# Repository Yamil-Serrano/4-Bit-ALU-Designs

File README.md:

# 4-Bit ALU Designs

A collection of 4-bit ALU implementations built entirely from discrete 74HC-series logic ICs. The project begins with a minimal ripple-carry architecture assembled on breadboard, then evolves into an expanded design featuring a 3-bit operation code and a dedicated PCB layout demonstrating how arithmetic and logic operations can be derived from fundamental gate-level building blocks.

# Hardware-Minimalist 4-bit ALU
This ALU represents the most fundamental version of the project: a design built entirely from discrete logic ICs, assembled by hand using breadboards, wiring, and basic digital components. The core idea is to show how a complete arithmetic and logic system can emerge from a minimal set of building blocks, following the principles of NAND universality and simple ripple-carry computation.

At its heart, this design implements a 4-bit ripple-carry adder, where each bit calculates its sum and pass its carry to the next stage. While not the fastest architecture, its transparency makes it highly educational: every step of the computation from XOR-based addition to AND-driven carry generation is physically observable in the circuit.

Beyond addition and subtraction, the ALU includes a NAND-based logic path to highlight how a single universal gate can serve as the foundation for more complex operations. The result is a compact but fully functional ALU that exemplifies hardware minimalism, discrete logic design, and hands-on digital engineering.

## Technical Specifications

### Core Features
- **Data Width**: 4-bit parallel processing
- **Operations**: 
  - `00` - Bitwise NAND (A NAND B)
  - `01` - Arithmetic addition (A + B)
  - `11` - Arithmetic subtraction (A - B) using two's complement
- **Control Input**: 2-bit operation code
- **Output Flags**: 
  - **Carry Out** - For arithmetic overflow detection
  - **Zero Flag** - Indicates when result equals 0000
- **Design Philosophy**: Hardware minimalism via NAND universality

## Integrated Circuits Used
| IC          | Function        | Quantity | Purpose                                        |
| ----------- | --------------- | -------- | ---------------------------------------------- |
| **74HC86**  | Quad XOR Gate   | 4        | Full adder implementation and two's complement |
| **74HC08**  | Quad AND Gate   | 2        | Carry generation for arithmetic operations     |
| **74HC00**  | Quad NAND Gate  | 1        | NAND operation and control logic               |
| **74HC157** | 2:1 Multiplexer | 1        | Operation selection and output routing         |
| **74HC4002**| Dual 4-Input NOR Gate | 1        | Zero detection             |

**Total Components:** 9 ICs implementing a complete 4-bit ALU

## Hardware Implementation

### Circuit Design

## Operation Details

#### 1. **Addition (01)**
- Implements 4-bit ripple-carry adder
- Uses XOR gates for sum, AND gates for carry
- Direct A + B computation

#### 2. **Subtraction (11)**
- Utilizes two's complement method
- Inverts B using XOR gates (B ⊕ 1)
- Adds 1 via carry-in for proper complement
- Result: A + (~B + 1) = A - B

#### 3. **NAND Operation (00)**
- Direct NAND gate implementation
- Demonstrates NAND universality principle
- Basis for emulating all other logic operations

### Flag Generation

#### **Zero Flag**
- Implemented using **74HC4002 Zero Detection Unit**
- Output: HIGH when result = 0000

#### **Carry Flag**
- Generated from the 4th full adder's carry-out
- Indicates arithmetic overflow in addition/subtraction

## Truth Table Examples

| A (bin) | B (bin) | Op | Result | Carry | Zero |
|---------|---------|----|--------|-------|------|
| 0101    | 0011    | 01 (Add) | 1000 | 0 | 0 |
| 0111    | 0010    | 11 (Sub) | 0101 | 1 | 0 |
| 1111    | 1111    | 00 (NAND) | 0000 | X | 1 |
| 0000    | 0000    | 01 (Add) | 0000 | 0 | 1 |

## Educational Value

This project demonstrates fundamental computer architecture concepts:

1. **NAND Universality**: All digital logic can be constructed from NAND gates
2. **Two's Complement Arithmetic**: How computers perform subtraction
3. **Hardware/Software Trade-off**: Why some operations are emulated in software
4. **Flag-Based Computing**: Essential for conditional operations in CPUs
5. **Ripple-Carry Design**: Basic but functional adder architecture

## ⚠️ Known Limitations

1. **Propagation Delay**: Ripple-carry design limits maximum speed
2. **Limited Operations**: Only 3 hardware operations
3. **No Overflow Flag**: Signed overflow detection not implemented

# Hardware-Minimalist 4-bit ALU (Modified 3-bit OP Code)

This updated version of the 4-bit minimalistic ALU introduces expanded operation selection while maintaining a fully discrete IC implementation. By replacing the 74HC157 with two 74HC153 multiplexers, the ALU can now handle five distinct operations controlled by a 3-bit operation code.

### Core Features

* **Data Width**: 4-bit parallel processing
* **Operations**:

  * `000` - Arithmetic Addition (A + B)
  * `100` - Arithmetic Subtraction (A - B) using two's complement
  * `X01` - Bitwise NAND (A NAND B)
  * `X10` - Bitwise XOR (A XOR B)
  * `X11` - Bitwise NOR (A NOR B)
* **Control Input**: 3-bit operation code
* **Output Flags**:

  * **Equal Flag** - Indicates when A equals B
  * **Zero Flag** - Indicates when ALU result equals 0000

### Integrated Circuits Used

| IC          | Function                   | Quantity | Purpose                                        |
| ----------- | -------------------------- | -------- | ---------------------------------------------- |
| **74HC86**  | Quad XOR Gate              | 5        | Full adder, two's complement, XOR operation    |
| **74HC08**  | Quad AND Gate              | 2        | Carry generation for arithmetic operations     |
| **74HC00**  | Quad NAND Gate             | 1        | NAND operation                                 |
| **74HC153** | Dual 4-input Multiplexer   | 2        | Selection between arithmetic and logic outputs |
| **74HC02**  | Quad NOR Gate              | 1        | NOR operation                                  |
| **74HC4002**| Dual 4-Input NOR Gate      | 1        | Zero and Equality detection                    |

**Total Components**: 12 ICs, implementing a complete 4-bit ALU with expanded functionality

## Hardware Implementation

### Circuit Design

### PCB Design in Kicad

After validating the architecture in simulation, the design was 
migrated from breadboard to a custom PCB manufactured via JLCPCB. 
Each IC is paired with a dedicated 100nF ceramic bypass capacitor
placed directly at the power pins to suppress switching noise. 
A 100µF bulk electrolytic capacitor stabilizes the 5V supply rail.

### Physical Build

## Verification & Test Bench

To validate correct operation across all input combinations, a dedicated test bench was developed using an ESP32 microcontroller. The [`firmware`](./src/tester/src) exhaustively tests all 256 input combinations (A × B, 0–15) for each of the 8 opcode states, and verifies both output flags across all cases totaling 2,048 flag assertions for the Zero flag alone.
All five operations passed with 100% accuracy across every input combination. Both the Equal flag and Zero flag returned correct results in every tested case. Results are reported over Serial with ANSI color coding, distinguishing passing opcodes in green from partial matches in yellow. A 20×4 LCD display connected via I2C provides a real-time progress bar during testing and a summary screen upon completion.

### Operation Details

#### 1. **Arithmetic Addition (000)**

* Implements 4-bit ripple-carry adder
* Uses XOR gates for sum, AND gates for carry
* Direct A + B computation

#### 2. **Arithmetic Subtraction (100)**

* Utilizes two's complement method
* Inverts B using XOR gates and adds 1 via carry-in
* Result: A + (~B + 1) = A - B

#### 3. **Bitwise NAND (X01)**

* Uses 74HC00 to implement NAND logic

#### 4. **Bitwise XOR (X10)**

* Uses additional 74HC86 to implement XOR logic

#### 5. **Bitwise NOR (X11)**

* Uses 74HC02 to implement NOR logic

### Flag Generation (Implemented using **74HC4002**)

* **Zero Flag**: HIGH when ALU output is 0000
* **Equal Flag**: HIGH when A is equal to B

### Truth Table Examples

| A (bin) | B (bin) | Op         | Result | Zero | Equal |
| ------- | ------- | ---------- | ------ | ---- | ----- |
| 0101    | 0011    | 000 (Add)  | 1000   | 0    | 0     |
| 0111    | 0010    | 100 (Sub)  | 0101   | 0    | 0     |
| 1111    | 1111    | X01 (NAND) | 0000   | 1    | 1     |
| 1010    | 0101    | X10 (XOR)  | 1111   | 0    | 0     |
| 1100    | 1010    | X11 (NOR)  | 0001   | 0    | 0     |

# FPGA Implementation: Tang Nano 9K
This module ports the 4-bit ALU logic from discrete integrated circuits to a programmable Gowin GW1NR-LV9 FPGA on the Sipeed Tang Nano 9K board. This transformation demonstrates a key modern digital design workflow: translating a proven hardware concept into a compact, single-chip solution using Hardware Description Language (HDL). The implementation faithfully replicates the behavior of the original breadboard circuit, providing a direct comparison between discrete and programmable logic.

## Physical Prototype & Interfacing
The FPGA interacts with the physical world through a simple, hands-on interface built on a breadboard. This setup mirrors the experience of the discrete version while showcasing the FPGA's role as a universal logic device.

## Design Philosophy & Notes
- **Architectural Fidelity**: The HDL description was structured to mirror the original ripple-carry data path, providing a clear one-to-one conceptual mapping between the discrete gate-level design and its HDL counterpart.
- **Resource Efficiency**: The entire system utilizes a very small fraction of the FPGA's available logic cells, demonstrating how a functional digital system can be miniaturized onto modern programmable logic.
- **Practical Focus**: The primary goal was a correct and understandable translation to HDL rather than performance optimization, maintaining the project's core educational value.

## Comparative Summary: Discrete vs. FPGA
This implementation highlights the practical differences between two hardware paradigms.

| Aspect | Discrete IC Implementation | FPGA Implementation |
| :--- | :--- | :--- |
| **Component Count** | 9 to 12 ICs, extensive wiring. | **1** primary chip. |
| **Design Method** | Wiring logic gates on a breadboard. | Writing and synthesizing HDL code. |
| **Flexibility** | Fixed; changes require physical rewiring. | **Reconfigurable** via code upload. |
| **Debugging** | Direct probing of every net with a multimeter. | Indirect, relying on synthesis reports and output observation. |
| **Core Experience** | Understanding gate-level data flow and propagation delay. | Learning the FPGA toolchain and HDL design patterns. |

## License
Licensed under the **Solderpad Hardware License v2.1**.  
See the [LICENSE](LICENSE-HARDWARE) file for full terms.

## Contact
If you have any questions or suggestions, feel free to reach out:
- **GitHub:** [Neowizen](https://github.com/Yamil-Serrano)

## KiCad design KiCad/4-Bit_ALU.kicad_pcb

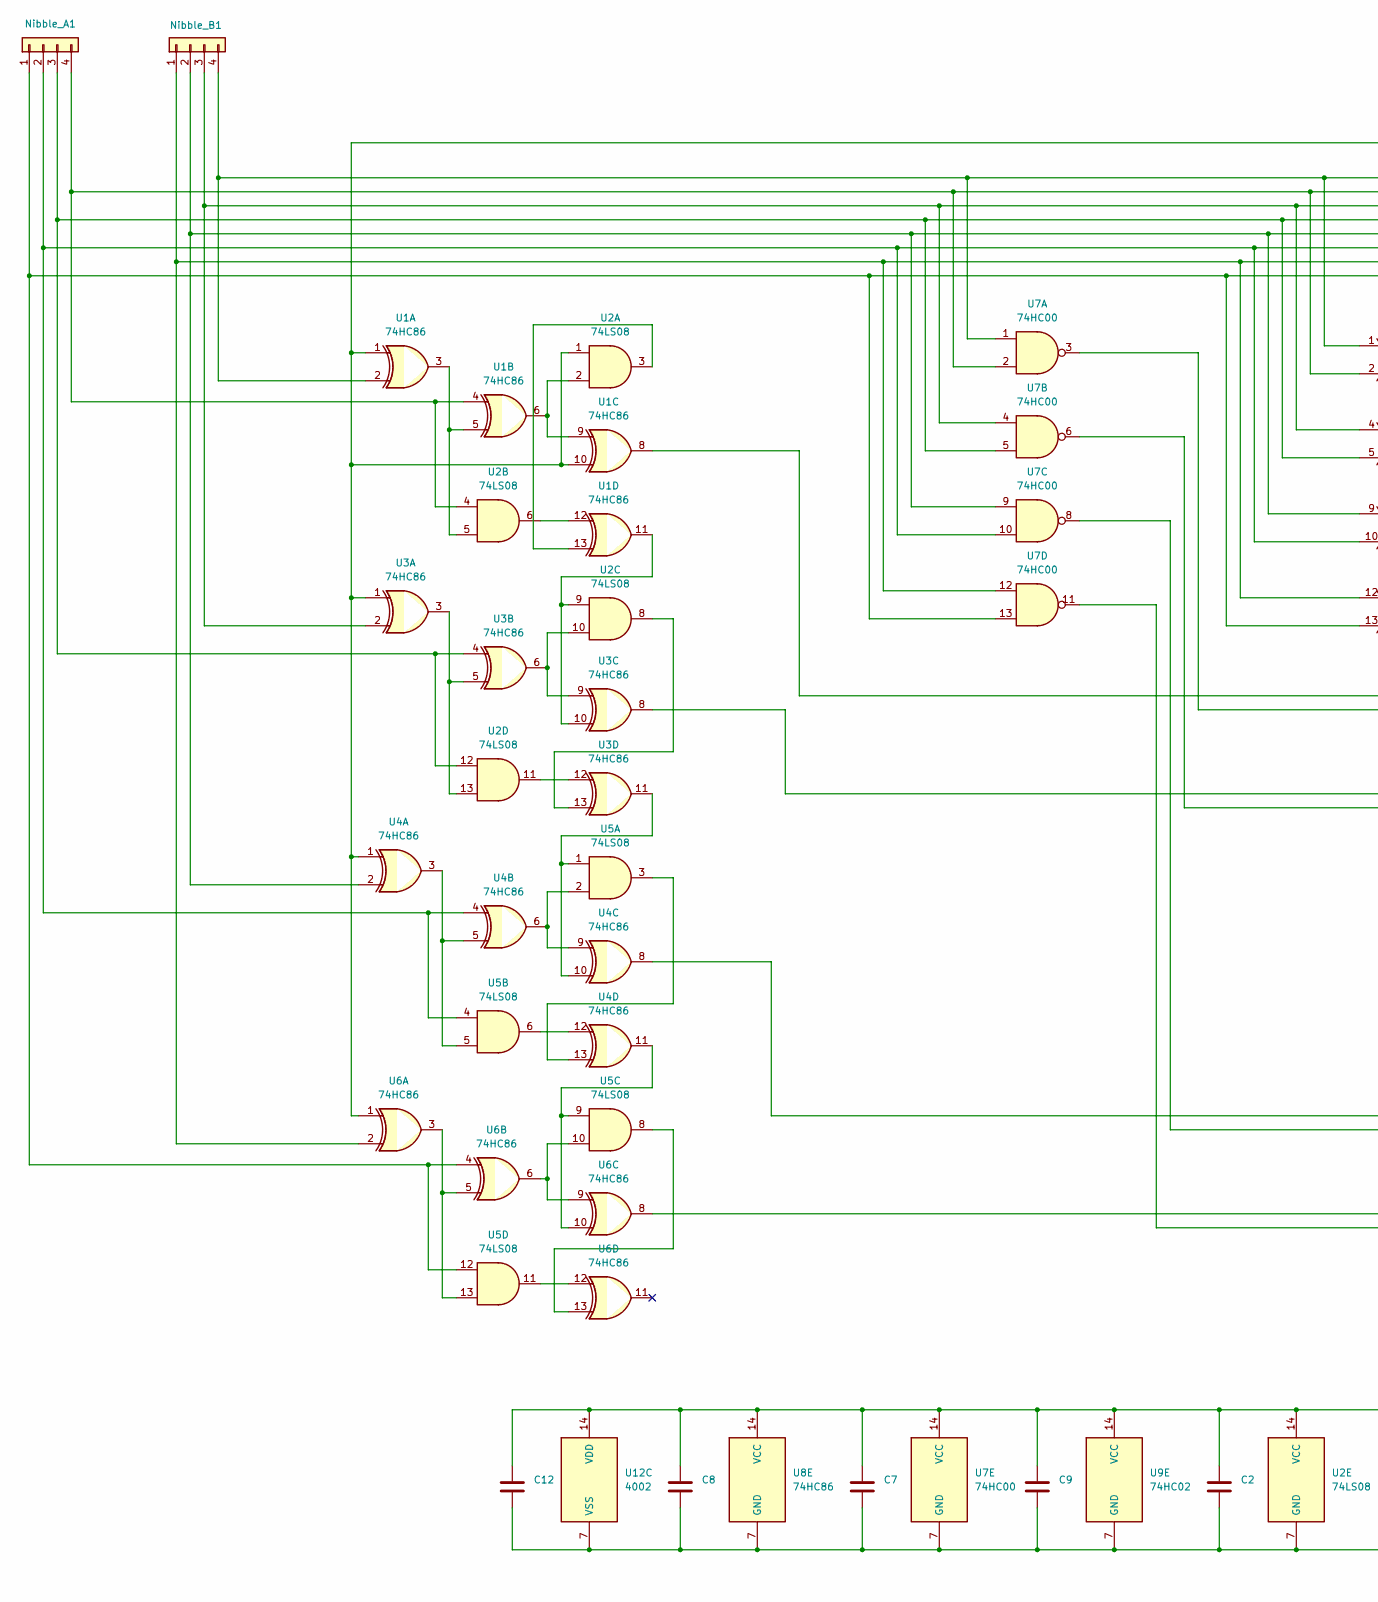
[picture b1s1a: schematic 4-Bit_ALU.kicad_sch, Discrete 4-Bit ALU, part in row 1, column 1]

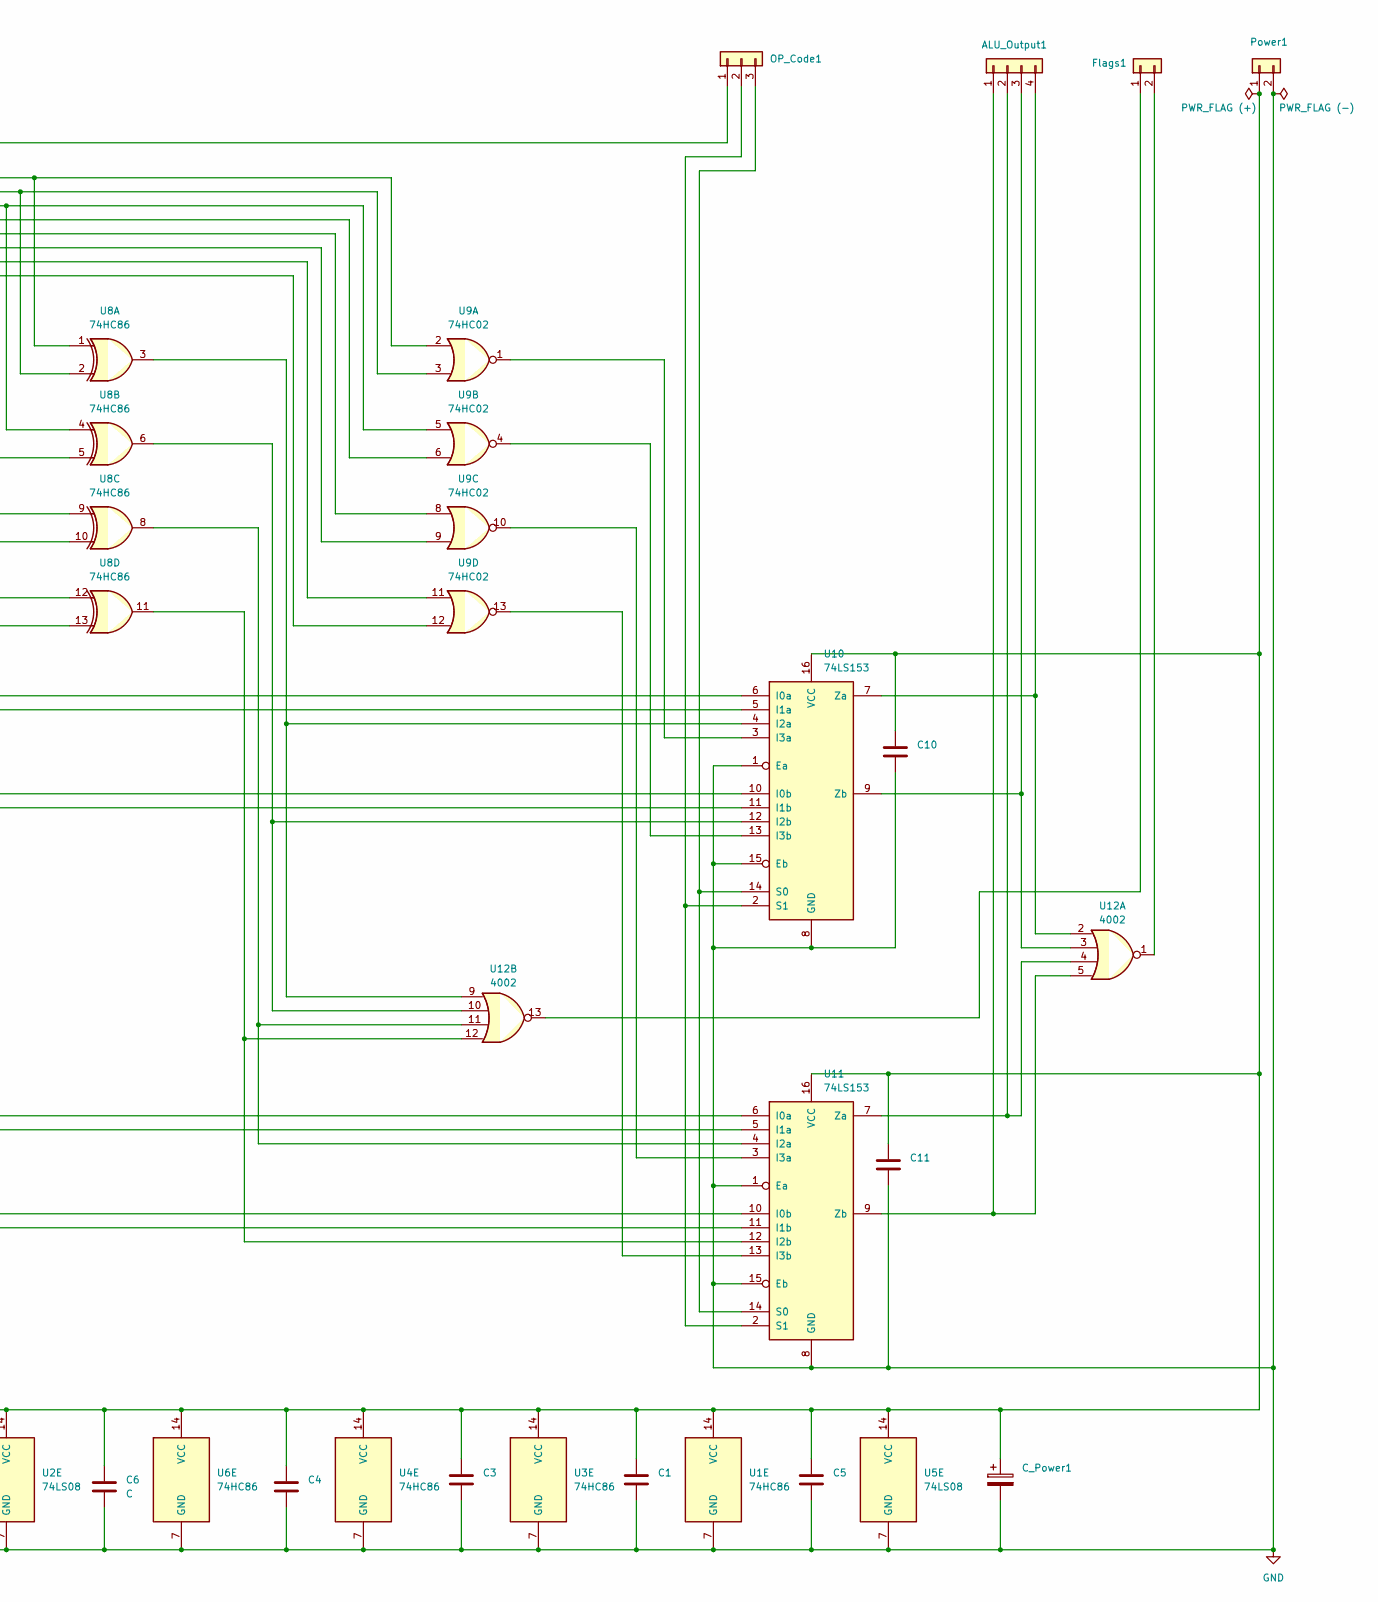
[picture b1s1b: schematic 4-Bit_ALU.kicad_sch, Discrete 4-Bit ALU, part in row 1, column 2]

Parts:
ALU_Output1: Conn_01x04; PinHeader_1x04_P2.54mm_Vertical
C1, C2, C3, C4, C5, C6, C7, C8, C9, C10, C11, C12: C; C_Disc_D3.0mm_W1.6mm_P2.50mm
C_Power1: C_Polarized; CP_Radial_D4.0mm_P1.50mm
Flags1: Conn_01x02; PinHeader_1x02_P2.54mm_Vertical
Nibble_A1: Conn_01x04; PinHeader_1x04_P2.54mm_Vertical
Nibble_B1: Conn_01x04; PinHeader_1x04_P2.54mm_Vertical
OP_Code1: Conn_01x03; PinHeader_1x03_P2.54mm_Vertical
Power1: Conn_01x02; PinHeader_1x02_P2.54mm_Vertical
U1, U3, U4, U6, U8: 74HC86; DIP-14_W7.62mm_Socket
U2, U5: 74LS08; DIP-14_W7.62mm_Socket
U7: 74HC00; DIP-14_W7.62mm_Socket
U9: 74HC02; DIP-14_W7.62mm_Socket
U10, U11: 74LS153; DIP-16_W7.62mm_Socket
U12: 4002; DIP-14_W7.62mm_Socket

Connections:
GND: C1.2, C2.2, C3.2, C4.2, C5.2, C6.2, C7.2, C8.2, C9.2, C10.2, C11.2, C12.2, C_Power1.2, Power1.2, U1.7 (GND), U2.7 (GND), U3.7 (GND), U4.7 (GND), U5.7 (GND), U6.7 (GND), U7.7 (GND), U8.7 (GND), U9.7 (GND), U10.1 (Ea), U10.8 (GND), U10.15 (Eb), U11.1 (Ea), U11.8 (GND), U11.15 (Eb), U12.7 (VSS)
unnamed: ALU_Output1.1, U11.9 (Zb), U12.5
unnamed: ALU_Output1.2, U11.7 (Za), U12.4
unnamed: ALU_Output1.3, U10.9 (Zb), U12.3
unnamed: ALU_Output1.4, U10.7 (Za), U12.2
unnamed: Flags1.1, U12.13
unnamed: Flags1.2, U12.1
unnamed: Nibble_A1.1, U5.12, U6.4, U7.13, U8.13, U9.12
unnamed: Nibble_A1.2, U4.4, U5.4, U7.10, U8.10, U9.9
unnamed: Nibble_A1.3, U2.12, U3.4, U7.5, U8.5, U9.6
unnamed: Nibble_A1.4, U1.4, U2.4, U7.2, U8.2, U9.3
unnamed: Nibble_B1.1, U6.2, U7.12, U8.12, U9.11
unnamed: Nibble_B1.2, U4.2, U7.9, U8.9, U9.8
unnamed: Nibble_B1.3, U3.2, U7.4, U8.4, U9.5
unnamed: Nibble_B1.4, U1.2, U7.1, U8.1, U9.2
unnamed: OP_Code1.1, U1.1, U1.10, U2.1, U3.1, U4.1, U6.1
unnamed: OP_Code1.2, U10.2 (S1), U11.2 (S1)
unnamed: OP_Code1.3, U10.14 (S0), U11.14 (S0)
unnamed: C1.1, C2.1, C3.1, C4.1, C5.1, C6.1, C7.1, C8.1, C9.1, C10.1, C11.1, C12.1, C_Power1.1, Power1.1, U1.14 (VCC), U2.14 (VCC), U3.14 (VCC), U4.14 (VCC), U5.14 (VCC), U6.14 (VCC), U7.14 (VCC), U8.14 (VCC), U9.14 (VCC), U10.16 (VCC), U11.16 (VCC), U12.14 (VDD)
unnamed: U1.3, U1.5, U2.5
unnamed: U1.6, U1.9, U2.2
unnamed: U1.11, U2.9, U3.10
unnamed: U1.12, U2.6
unnamed: U1.13, U2.3
unnamed: U2.8, U3.13
unnamed: U2.10, U3.6, U3.9
unnamed: U2.11, U3.12
unnamed: U2.13, U3.3, U3.5
unnamed: U3.11, U4.10, U5.1
unnamed: U4.3, U4.5, U5.5
unnamed: U4.6, U4.9, U5.2
unnamed: U4.11, U5.9, U6.10
unnamed: U4.12, U5.6
unnamed: U4.13, U5.3
unnamed: U5.8, U6.13
unnamed: U5.10, U6.6, U6.9
unnamed: U5.11, U6.12
unnamed: U5.13, U6.3, U6.5
unnamed: U1.8, U10.6 (I0a)
unnamed: U3.8, U10.10 (I0b)
unnamed: U7.3, U10.5 (I1a)
unnamed: U7.6, U10.11 (I1b)
unnamed: U8.3, U10.4 (I2a), U12.9
unnamed: U8.6, U10.12 (I2b), U12.10
unnamed: U9.1, U10.3 (I3a)
unnamed: U9.4, U10.13 (I3b)
unnamed: U4.8, U11.6 (I0a)
unnamed: U6.8, U11.10 (I0b)
unnamed: U7.8, U11.5 (I1a)
unnamed: U7.11, U11.11 (I1b)
unnamed: U8.8, U11.4 (I2a), U12.11
unnamed: U8.11, U11.12 (I2b), U12.12
unnamed: U9.10, U11.3 (I3a)
unnamed: U9.13, U11.13 (I3b)

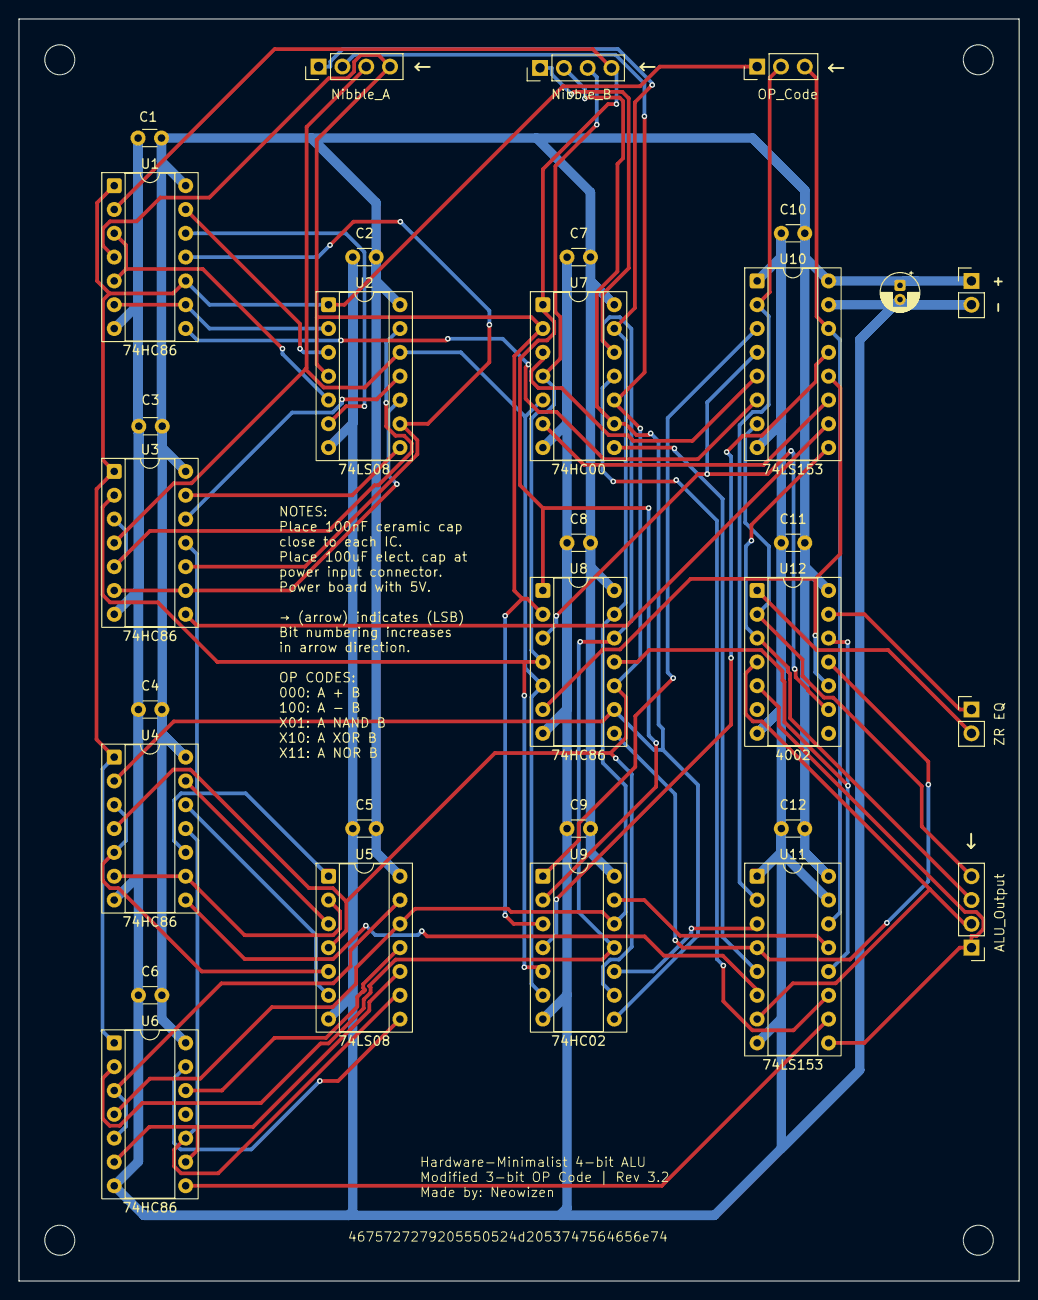
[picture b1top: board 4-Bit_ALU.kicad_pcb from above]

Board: 2 copper layers, 106.7 x 134.6 mm, 31 parts (0 on the bottom side), 54 nets.

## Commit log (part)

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2025-12-07 Enhance README with detailed project information
    Expanded the README to include detailed project description, technical specifications, integrated circuits used, operation details, educational value, components list, construction tips, and known li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
2025-12-09 Expand README with Advanced ALU information
    Added details about the Advanced Carry-Lookahead ALU, including its benefits, additional logic operations, and FPGA-oriented implementation.
2025-12-11 Replace image in README for CLA section
    Updated image source for the Carry-Lookahead Logic section.
2025-12-20 Add Solderpad Hardware License v2.1
2025-12-20 Fix link to LICENSE file in README
2026-05-20 Revise README for ALU design updates and testing
    Updated the README to reflect changes in ALU designs, including a new PCB design and test bench validation using an ESP32 microcontroller. Removed outdated components and added details on operation c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
2026-05-22 Add test firmware, configuration files and README updates
2026-06-02 Refactor ALU module and add comprehensive testbench for functionality verification
2026-06-05 Tester updated for arduino and esp32
2026-06-07 Add 4-Bit ALU KiCad project
